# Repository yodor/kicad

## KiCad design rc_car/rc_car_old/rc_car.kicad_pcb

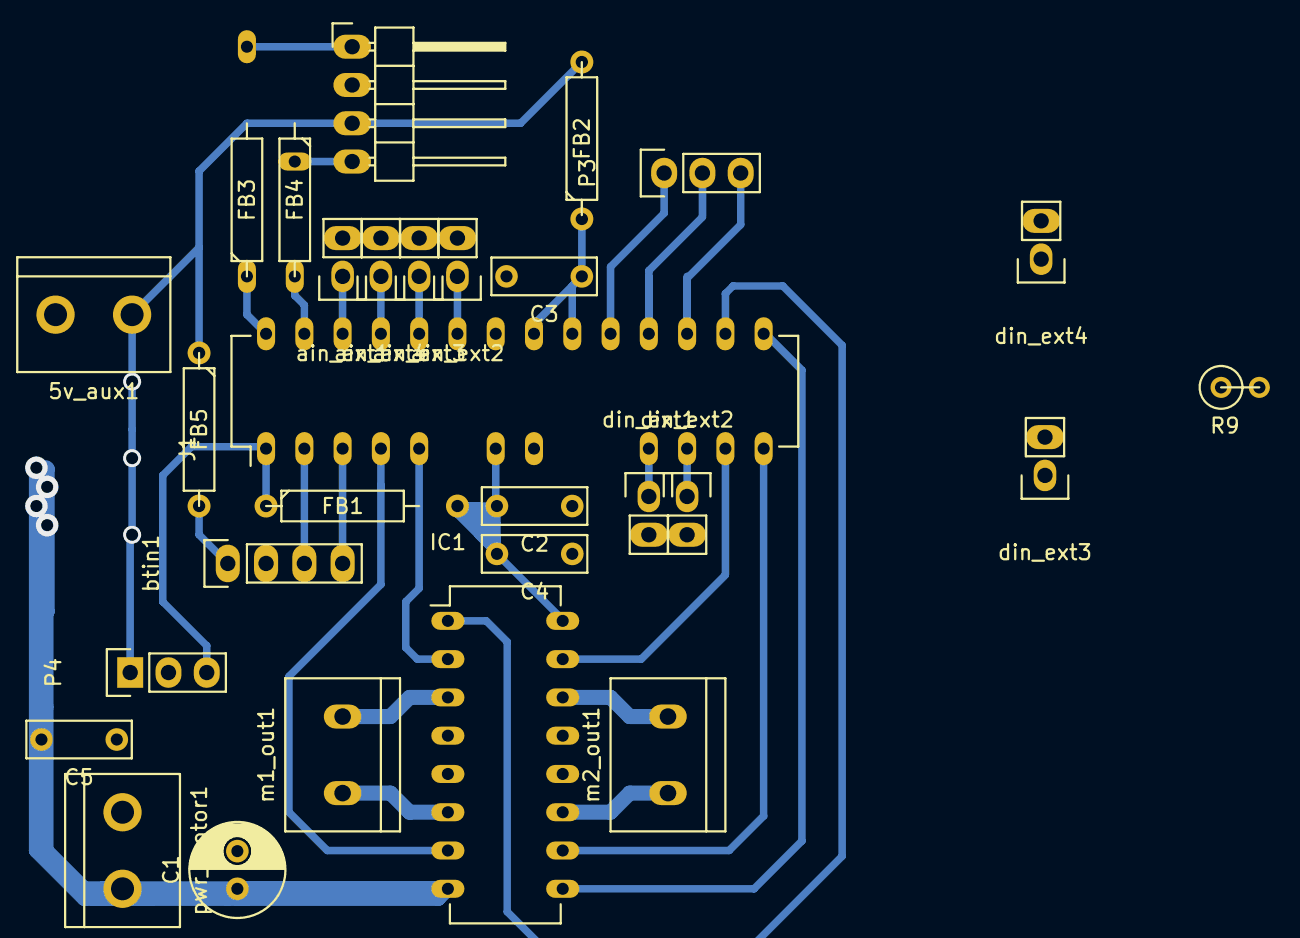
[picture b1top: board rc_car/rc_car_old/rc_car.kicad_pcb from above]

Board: 2 copper layers, 29 parts (0 on the bottom side), 33 nets.

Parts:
5v_aux1: CONN_2; bornier2
C1: 470uF; C_Radial_D6.3_L11.2_P2.5
C2, C3, C5: 100nF; C_Rect_L7_W2.5_P5
C4: 100n; C_Rect_L7_W2.5_P5
FB1, FB2, FB3, FB4, FB5: FILTER; R4
IC1: L293D; DIP-16_W7.62mm_LongPads
J1: Atmega328; DIP-28_W7.62mm_LongPads
P3, P4: CONN_01X03; Pin_Header_Straight_1x03
R9: 10K; R1
ain_ext1, ain_ext2, ain_ext3, ain_ext4: CONN_2; Pin_Header_Straight_1x02
btin1: CONN_4; Pin_Header_Straight_1x04
din_ext1, din_ext2, din_ext3, din_ext4: CONN_2; Pin_Header_Straight_1x02
i2c1: CONN_4; Pin_Header_Angled_1x04
m1_out1, m2_out1: CONN_2; bornier2
pwr_motor1: CONN_2; bornier2

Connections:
/5V: 5v_aux1.1, FB1.1, FB2.2, FB5.1, P4.1, R9.1, i2c1.3
/5V_FILTER: C2.2, C4.2, FB1.2, IC1.16, J1.7
/5V_FILTER_BT: FB5.2, btin1.1
/A0: J1.23, ain_ext2.1
/A1: J1.24, ain_ext3.1
/A2: J1.25, ain_ext4.1
/A3: J1.26, ain_ext1.1
/D1: J1.11, din_ext1.1
/D2: J1.12, din_ext2.1
/M1_EN: IC1.1, J1.16
/M1_L: IC1.2, J1.5
/M1_OUT_L: IC1.3, m1_out1.2
/M1_OUT_R: IC1.6, m1_out1.1
/M1_R: IC1.7, J1.4
/M2_EN: IC1.9, J1.15
/M2_L: IC1.15, J1.13
/M2_OUT_L: IC1.14, m2_out1.2
/M2_OUT_R: IC1.11, m2_out1.1
/M2_R: IC1.10, J1.14
/MISO: J1.18, P3.2
/MOSI: J1.17, P3.3
/RST: J1.1, P4.3, R9.2
/RX: J1.2, btin1.3
/SCK: J1.19, P3.1
/SCL: FB3.2, i2c1.1
/SDA: FB4.1, i2c1.4
/TX: J1.3, btin1.4
/VIN_MOTOR: C1.1, C5.2, IC1.8, pwr_motor1.2
GND: 5v_aux1.2, C2.1, C3.2, C4.1, C5.1, IC1.4, IC1.5, IC1.12, IC1.13, J1.8, J1.22, P4.2, ain_ext1.2, ain_ext2.2, ain_ext3.2, ain_ext4.2, btin1.2, din_ext1.2, din_ext2.2, din_ext3.2, din_ext4.2, i2c1.2
GNDREF: C1.2, pwr_motor1.1
unnamed: C3.1, FB2.1, J1.20, J1.21
unnamed: FB3.1, J1.28
unnamed: FB4.2, J1.27

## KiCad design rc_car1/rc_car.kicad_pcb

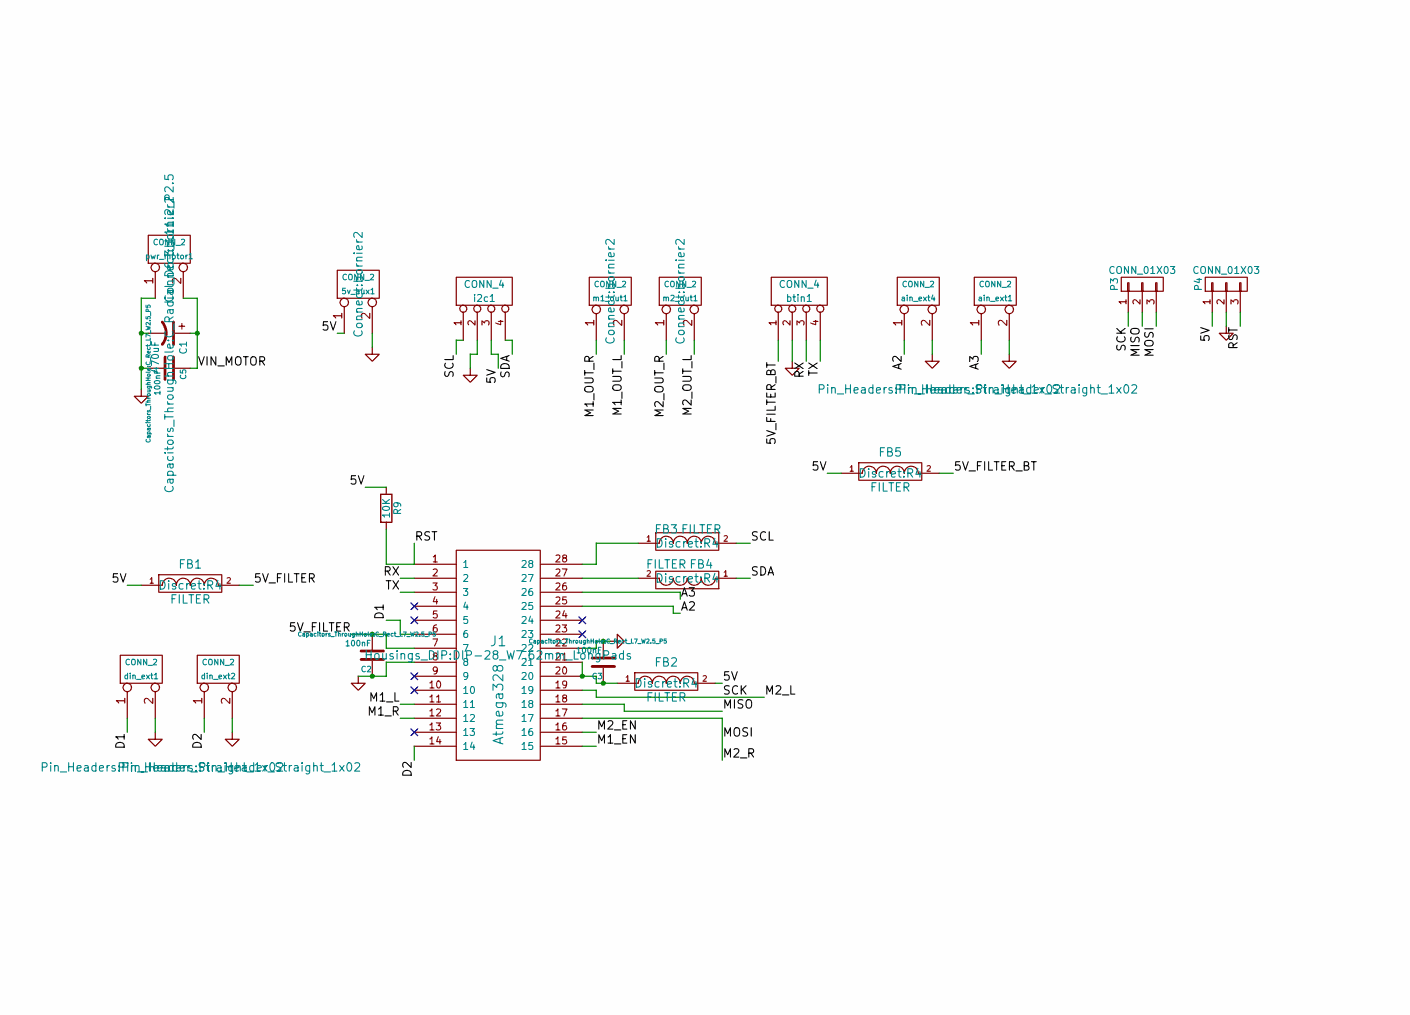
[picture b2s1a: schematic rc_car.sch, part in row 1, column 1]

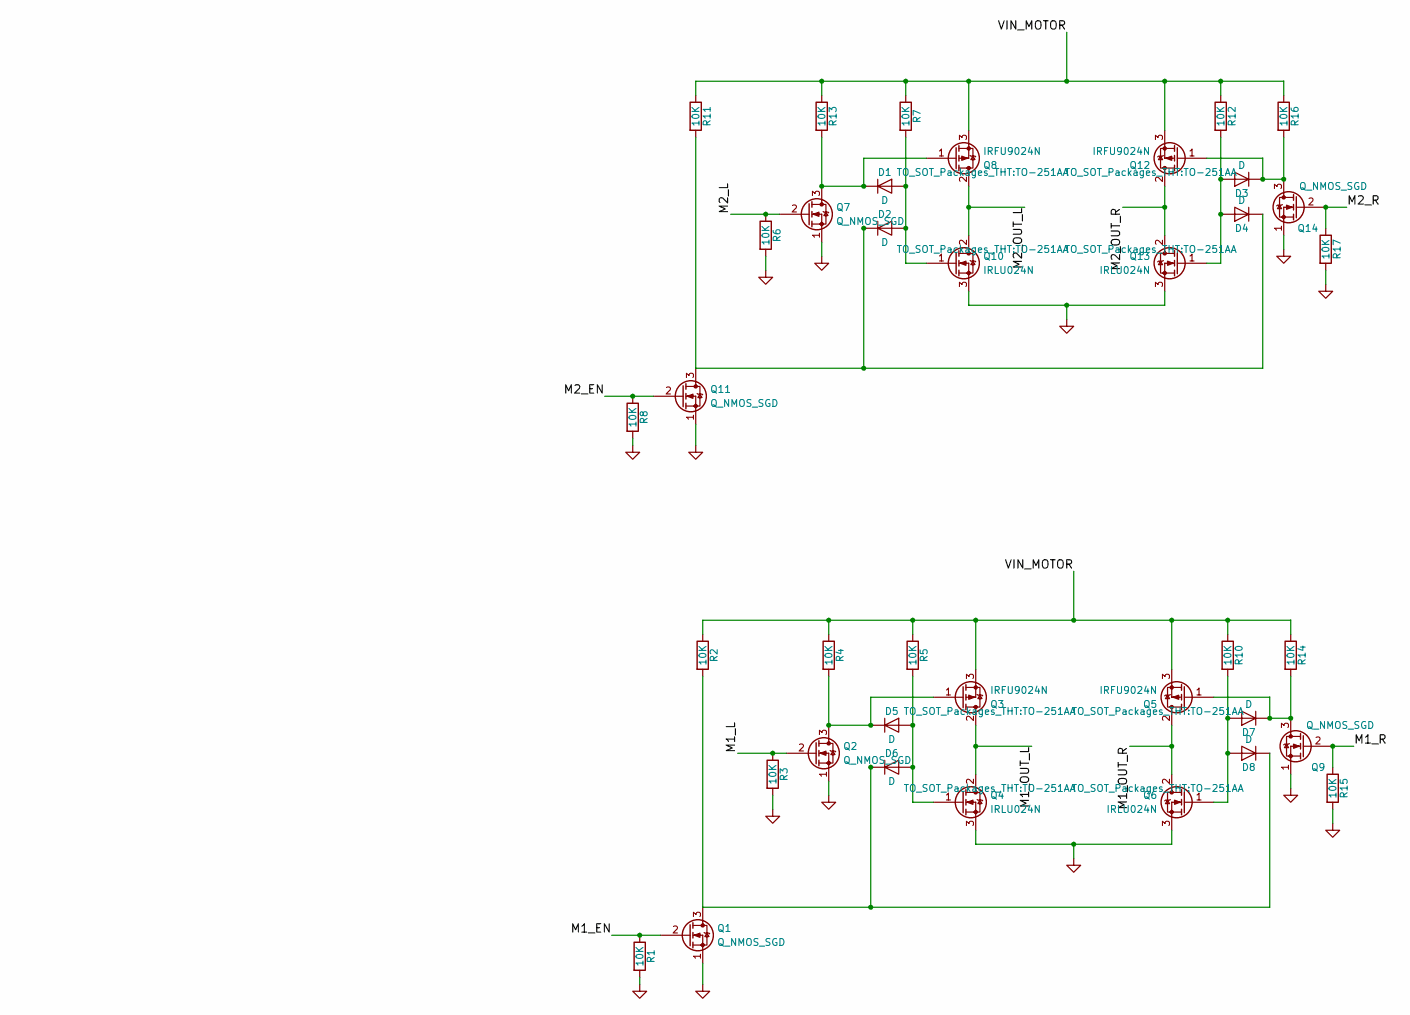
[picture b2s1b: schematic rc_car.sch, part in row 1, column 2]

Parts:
5v_aux1: CONN_2; bornier2
C1: 470uF; C_Radial_D6.3_L11.2_P2.5
C2, C3, C5: 100nF; C_Rect_L7_W2.5_P5
D1, D2, D3, D4, D5, D6, D7, D8: D; DO-41
FB1, FB2, FB3, FB4, FB5: FILTER; R4
J1: Atmega328; DIP-28_W7.62mm_LongPads
P3, P4: CONN_01X03; Pin_Header_Straight_1x03
Q1, Q2, Q7, Q9, Q11, Q14: Q_NMOS_SGD; TO-92_Inline_Narrow_Oval
Q3, Q5, Q8, Q12: IRFU9024N; TO-251AA
Q4, Q6, Q10, Q13: IRLU024N; TO-251AA
R1, R3, R6, R8, R14, R15, R16, R17: 10K; R1
R2, R4, R5, R7, R9, R10, R11, R12, R13: 10K; R4
ain_ext1, ain_ext4: CONN_2; Pin_Header_Straight_1x02
btin1: CONN_4; Pin_Header_Straight_1x04
din_ext1, din_ext2: CONN_2; Pin_Header_Straight_1x02
i2c1: CONN_4; Pin_Header_Angled_1x04
m1_out1, m2_out1: CONN_2; bornier2
pwr_motor1: CONN_2; bornier2

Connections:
/5V: 5v_aux1.1, FB1.1, FB2.2, FB5.1, P4.1, R9.1, i2c1.3
/5V_FILTER: C2.2, FB1.2, J1.7
/5V_FILTER_BT: FB5.2, btin1.1
/A2: J1.25, ain_ext4.1
/A3: J1.26, ain_ext1.1
/D1: J1.6, din_ext1.1
/D2: J1.14, din_ext2.1
/M1_EN: J1.15, Q1.2 (G), R1.1
/M1_L: J1.11, Q2.2 (G), R3.1
/M1_OUT_L: Q3.2 (D), Q4.2 (D), m1_out1.2 (PM)
/M1_OUT_R: Q5.2 (D), Q6.2 (D), m1_out1.1
/M1_R: J1.12, Q9.2 (G), R15.1
/M2_EN: J1.16, Q11.2 (G), R8.1
/M2_L: J1.19, P3.1, Q7.2 (G), R6.1
/M2_OUT_L: Q8.2 (D), Q10.2 (D), m2_out1.2 (PM)
/M2_OUT_R: Q12.2 (D), Q13.2 (D), m2_out1.1
/M2_R: J1.17, P3.3, Q14.2 (G), R17.1
/MISO: J1.18, P3.2
/RST: J1.1, P4.3, R9.2
/RX: J1.2, btin1.3
/SCL: FB3.2, i2c1.1
/SDA: FB4.1, i2c1.4
/TX: J1.3, btin1.4
/VIN_MOTOR: C1.1, C5.1, Q3.3 (S), Q5.3 (S), Q8.3 (S), Q12.3 (S), R2.1, R4.1, R5.1, R7.1, R10.1, R11.1, R12.1, R13.1, R14.1, R16.1, pwr_motor1.2 (PM)
GND: 5v_aux1.2 (PM), C1.2, C2.1, C3.2, C5.2, J1.8, J1.22, P4.2, Q1.1 (S), Q2.1 (S), Q4.3 (S), Q6.3 (S), Q7.1 (S), Q9.1 (S), Q10.3 (S), Q11.1 (S), Q13.3 (S), Q14.1 (S), R1.2, R3.2, R6.2, R8.2, R15.2, R17.2, ain_ext1.2 (PM), ain_ext4.2 (PM), btin1.2, din_ext1.2 (PM), din_ext2.2 (PM), i2c1.2, pwr_motor1.1
unnamed: C3.1, FB2.1, J1.20, J1.21
unnamed: D1.1 (K), Q7.3 (D), Q8.1 (G), R13.2
unnamed: D1.2 (A), D2.2 (A), Q10.1 (G), R7.2
unnamed: D2.1 (K), D4.1 (K), Q11.3 (D), R11.2
unnamed: D3.1 (K), Q12.1 (G), Q14.3 (D), R16.2
unnamed: D3.2 (A), D4.2 (A), Q13.1 (G), R12.2
unnamed: D5.1 (K), Q2.3 (D), Q3.1 (G), R4.2
unnamed: D5.2 (A), D6.2 (A), Q4.1 (G), R5.2
unnamed: D6.1 (K), D8.1 (K), Q1.3 (D), R2.2
unnamed: D7.1 (K), Q5.1 (G), Q9.3 (D), R14.2
unnamed: D7.2 (A), D8.2 (A), Q6.1 (G), R10.2
unnamed: FB3.1, J1.28
unnamed: FB4.2, J1.27

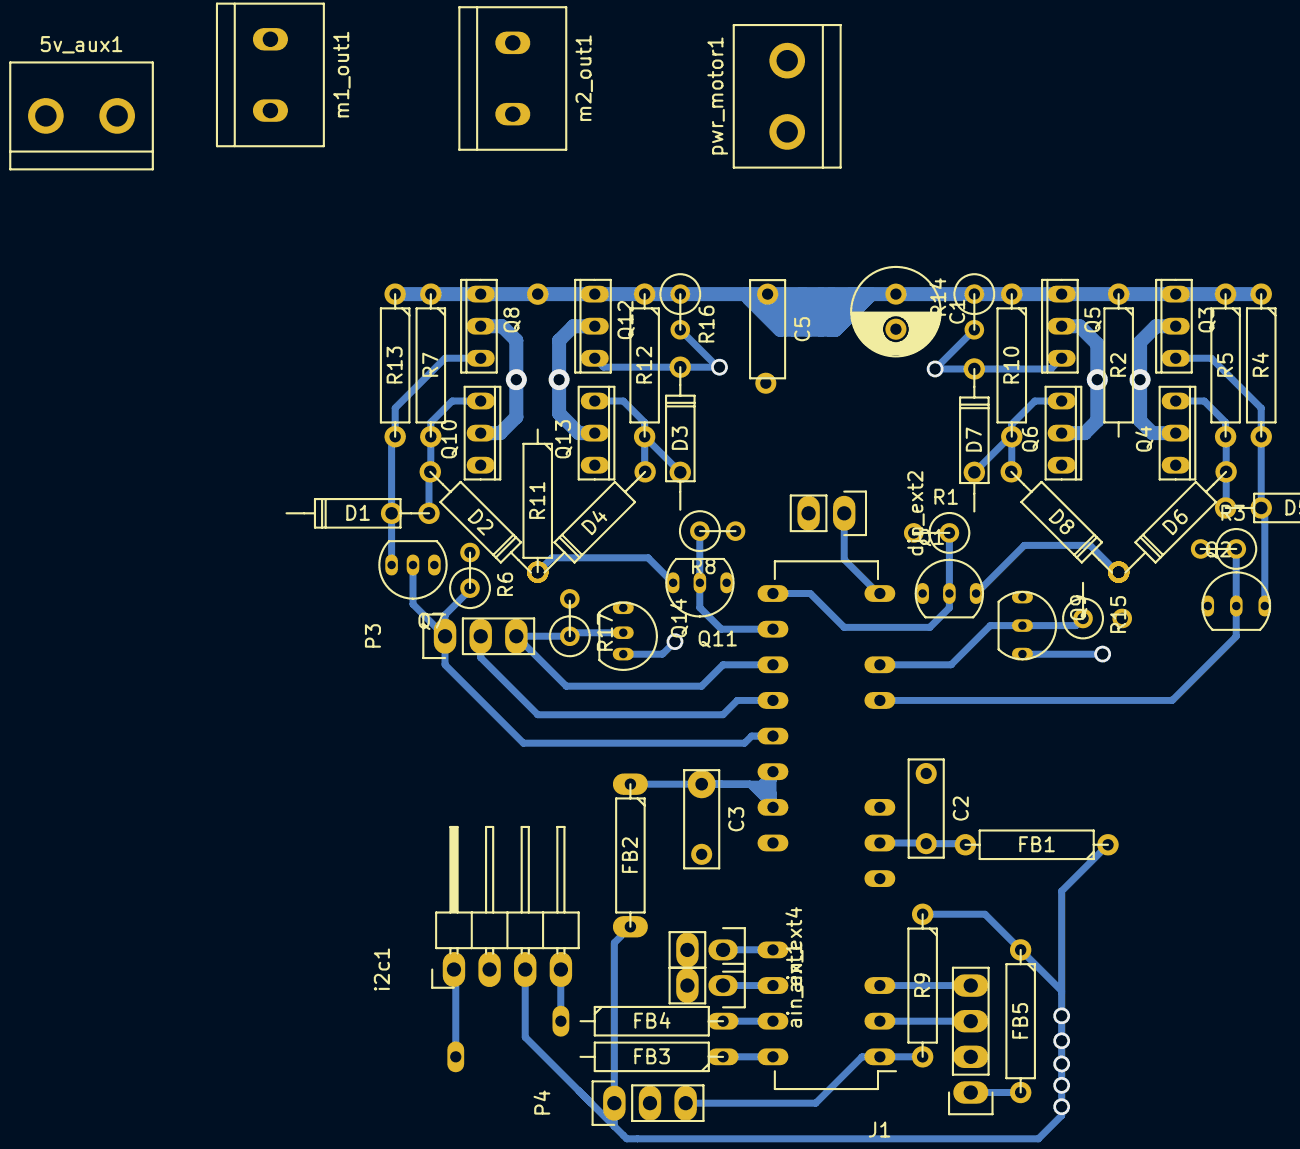
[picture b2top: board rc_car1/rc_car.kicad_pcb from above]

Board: 2 copper layers, 60 parts (0 on the bottom side), 37 nets.

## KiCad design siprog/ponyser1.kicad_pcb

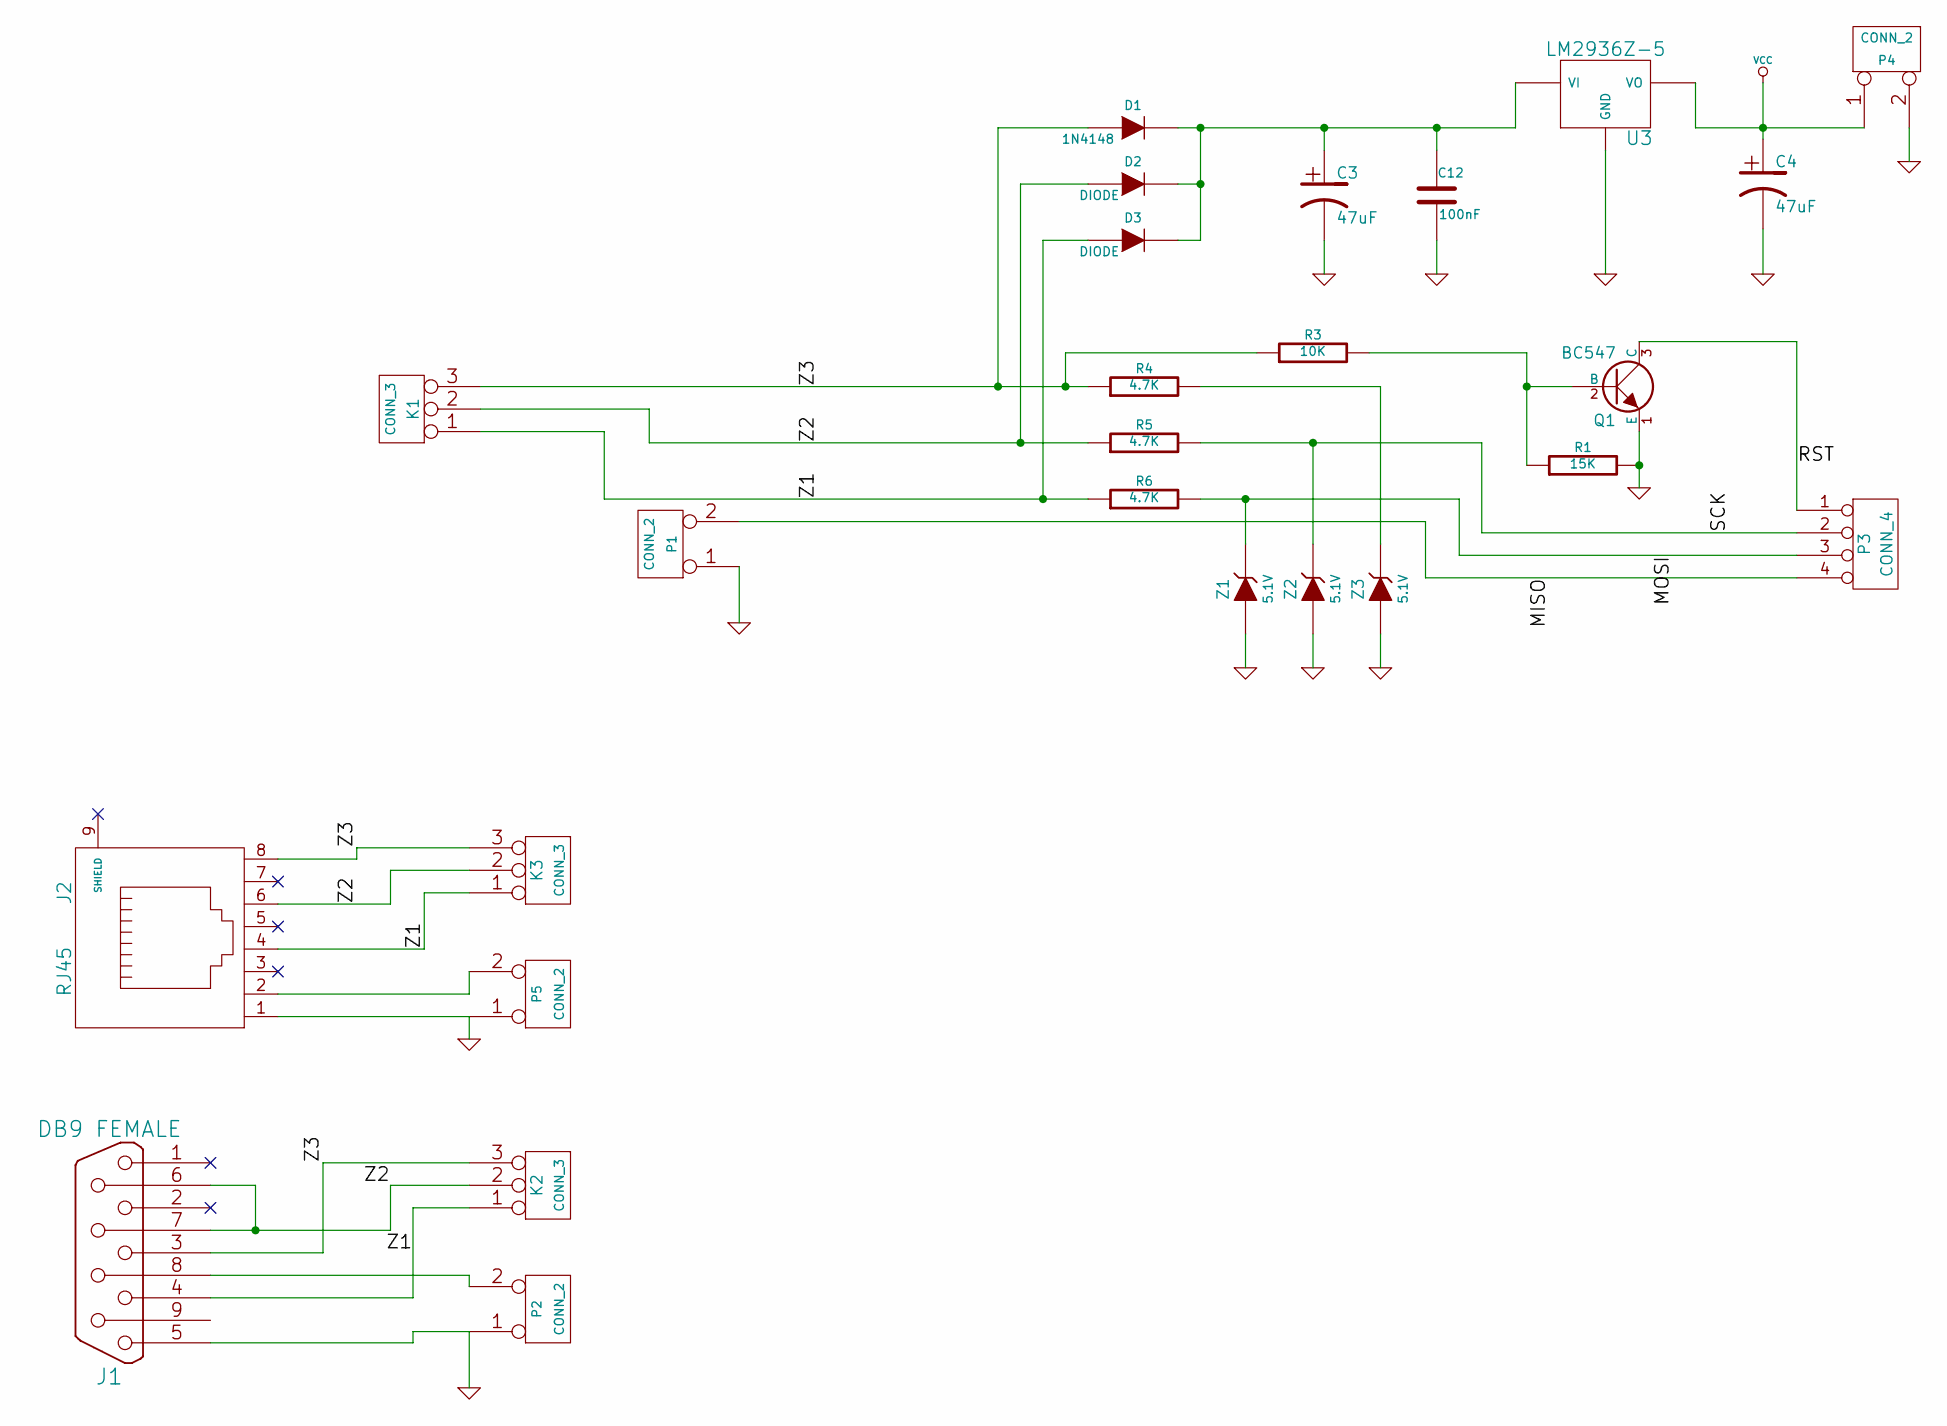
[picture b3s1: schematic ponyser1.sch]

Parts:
C3, C4: 47uF
C12: 100nF
D1: 1N4148
D2, D3: DIODE
J1: DB9 FEMALE
J2: RJ45
K1, K2, K3: CONN_3
P1, P2, P4, P5: CONN_2
P3: CONN_4
Q1: BC547
R1: 15K
R3: 10K
R4, R5, R6: 4.7K
U3: LM2936Z-5
Z1, Z2, Z3: 5.1V

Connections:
/MISO: P1.2 (PM), P3.4
/MOSI: P3.3, R6.2, Z1.2 (K)
/RST: P3.1, Q1.3 (C)
/SCK: P3.2, R5.2, Z2.2 (K)
/Z1: D3.1 (A), J1.4, J2.4, K1.1, K2.1, K3.1, R6.1
/Z2: D2.1 (A), J1.6, J1.7, J2.6, K1.2 (PM), K2.2 (PM), K3.2 (PM), R5.1
/Z3: D1.1 (A), J1.3, J2.8, K1.3, K2.3, K3.3, R3.1, R4.1
GND: C3.2, C4.2, C12.2, J1.5, J2.1, P1.1, P2.1, P4.2 (PM), P5.1, Q1.1 (E), R1.2, U3.GND, Z1.1 (A), Z2.1 (A), Z3.1 (A)
unnamed: Q1.2 (B), R1.1, R3.2
unnamed: C3.1, C12.1, D1.2 (K), D2.2 (K), D3.2 (K), U3.VI
unnamed: J2.2, P5.2 (PM)
unnamed: J1.8, P2.2 (PM)
unnamed: R4.2, Z3.2 (K)
VCC: C4.1, P4.1, U3.VO

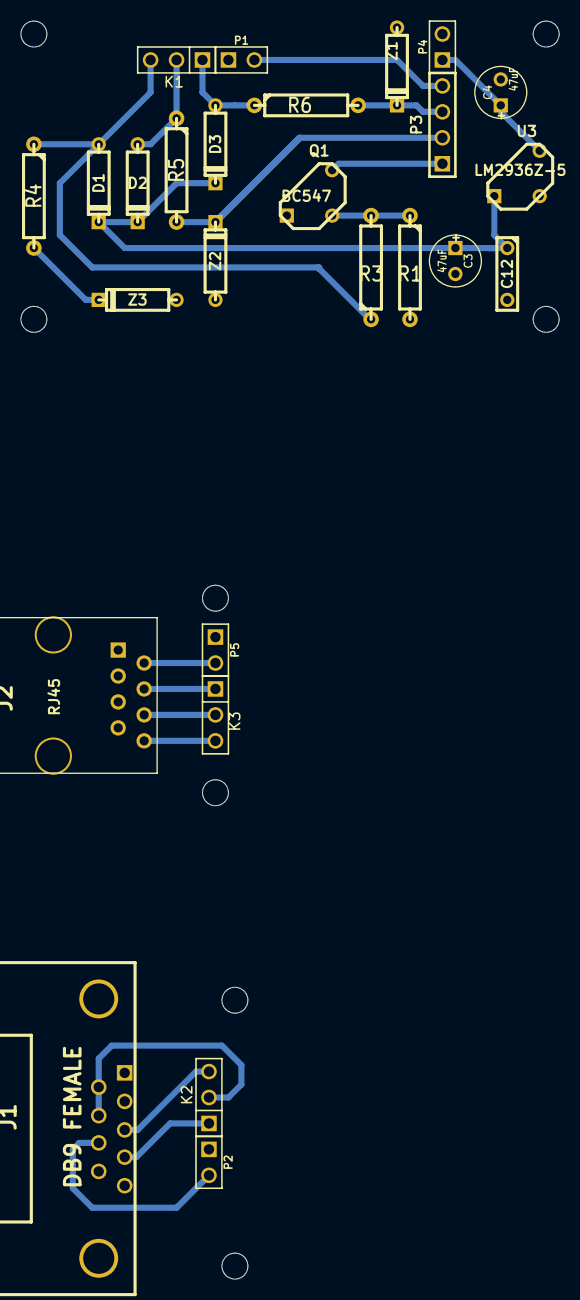
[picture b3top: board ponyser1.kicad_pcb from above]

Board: 2 copper layers, 52.7 x 123.2 mm, 26 parts (0 on the bottom side), 14 nets.

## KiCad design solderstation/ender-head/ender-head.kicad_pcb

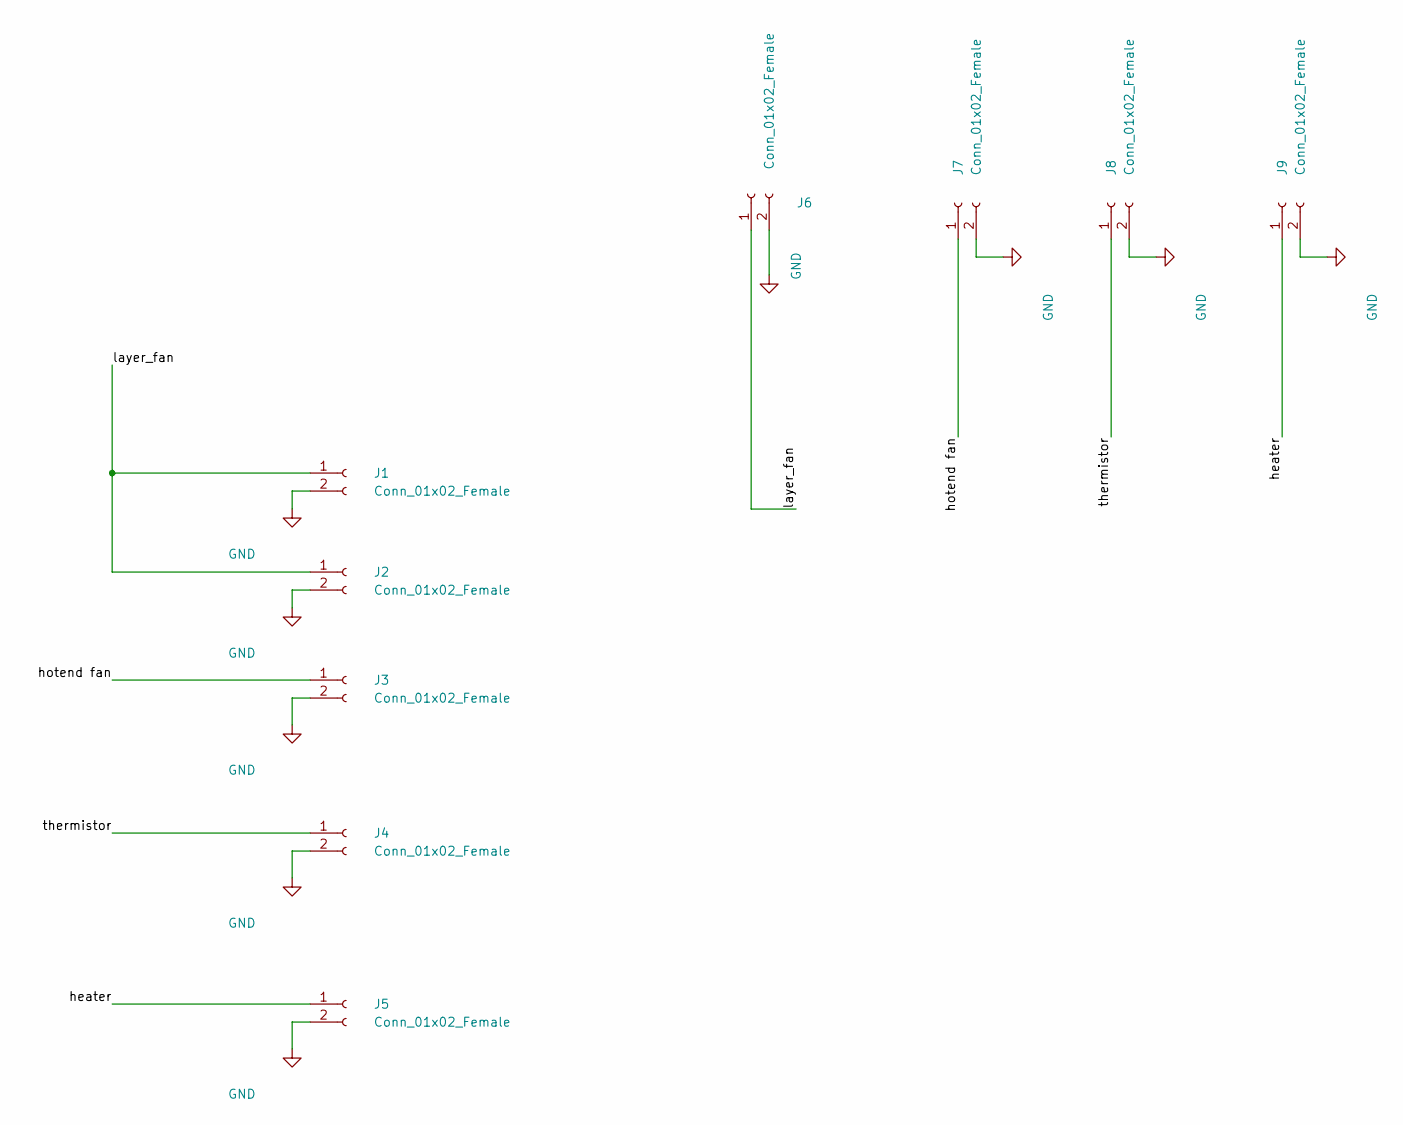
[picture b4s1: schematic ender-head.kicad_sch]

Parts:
J1, J2, J3, J4, J5: Conn_01x02_Female; TerminalBlock_bornier-2_P5.08mm
J6, J7, J8: Conn_01x02_Female; PinHeader_1x02_P2.54mm_Vertical
J9: Conn_01x02_Female; AMASS_XT60-M_1x02_P7.20mm_Vertical

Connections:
/heater: J5.1, J9.1
/hotend fan: J3.1, J7.1
/layer_fan: J1.1, J2.1, J6.1
/thermistor: J4.1, J8.1
GND: J1.2, J2.2, J3.2, J4.2, J5.2, J6.2, J7.2, J8.2, J9.2

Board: 2 copper layers, 9 parts (0 on the bottom side), 5 nets, no tracks yet.

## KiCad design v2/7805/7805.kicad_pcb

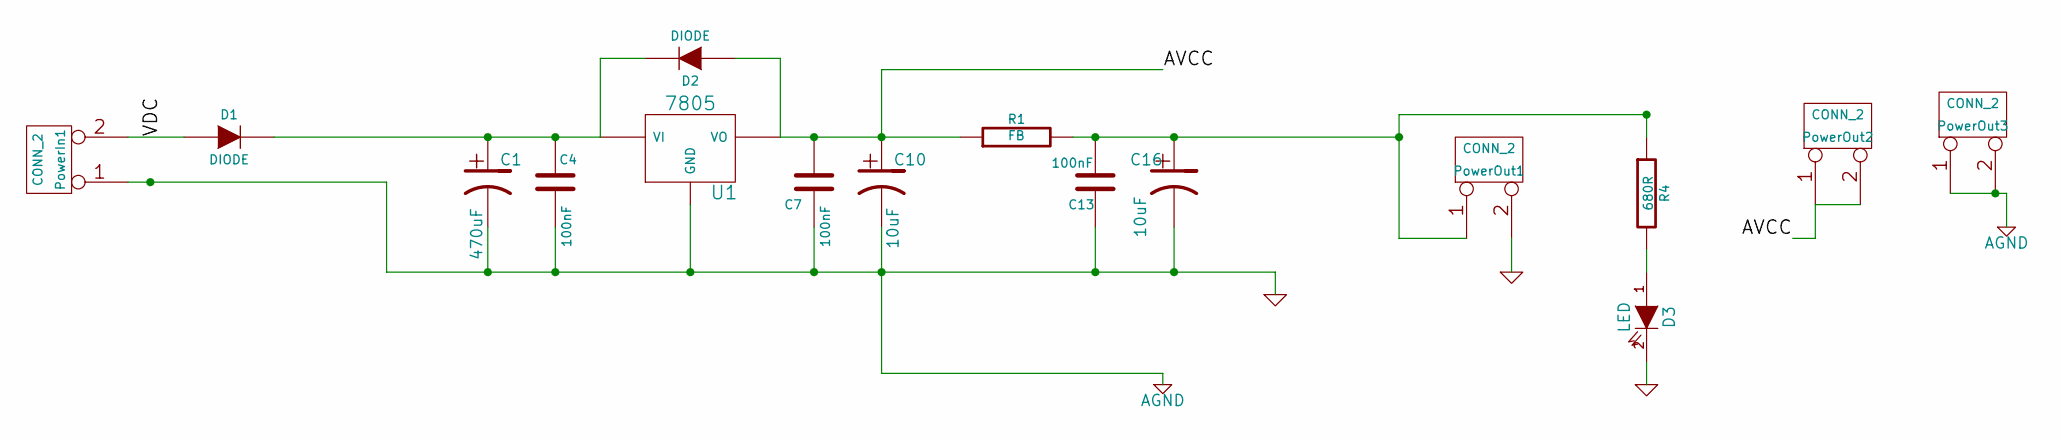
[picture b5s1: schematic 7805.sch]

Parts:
C1: 470uF
C4, C7, C13: 100nF
C10, C16: 10uF
D1, D2: DIODE
D3: LED
PowerIn1: CONN_2
PowerOut1, PowerOut2, PowerOut3: CONN_2
R1: FB
R4: 680R
U1: 7805

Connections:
/AVCC: C7.2, C10.1, D2.1 (A), PowerOut2.1, PowerOut2.2 (PM), R1.1, U1.VO
/VDC: D1.1 (A), PowerIn1.2 (PM)
AGND: C1.2, C4.1, C7.1, C10.2, C13.1, C16.2, D3.2 (K), PowerIn1.1, PowerOut1.2 (PM), PowerOut3.1, PowerOut3.2 (PM), U1.GND
unnamed: C13.2, C16.1, PowerOut1.1, R1.2, R4.1
unnamed: C1.1, C4.2, D1.2 (K), D2.2 (K), U1.VI
unnamed: D3.1 (A), R4.2

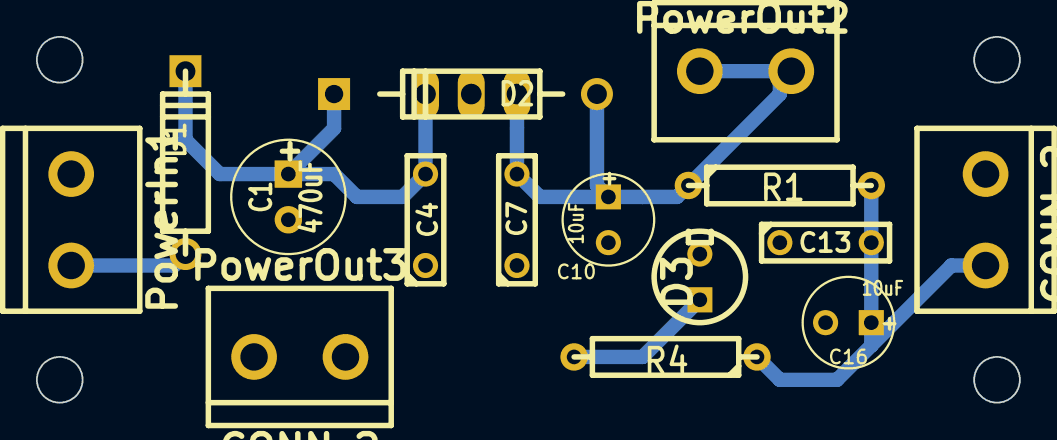
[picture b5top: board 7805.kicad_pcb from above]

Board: 2 copper layers, 54.6 x 20.3 mm, 16 parts (1 on the bottom side), 6 nets.

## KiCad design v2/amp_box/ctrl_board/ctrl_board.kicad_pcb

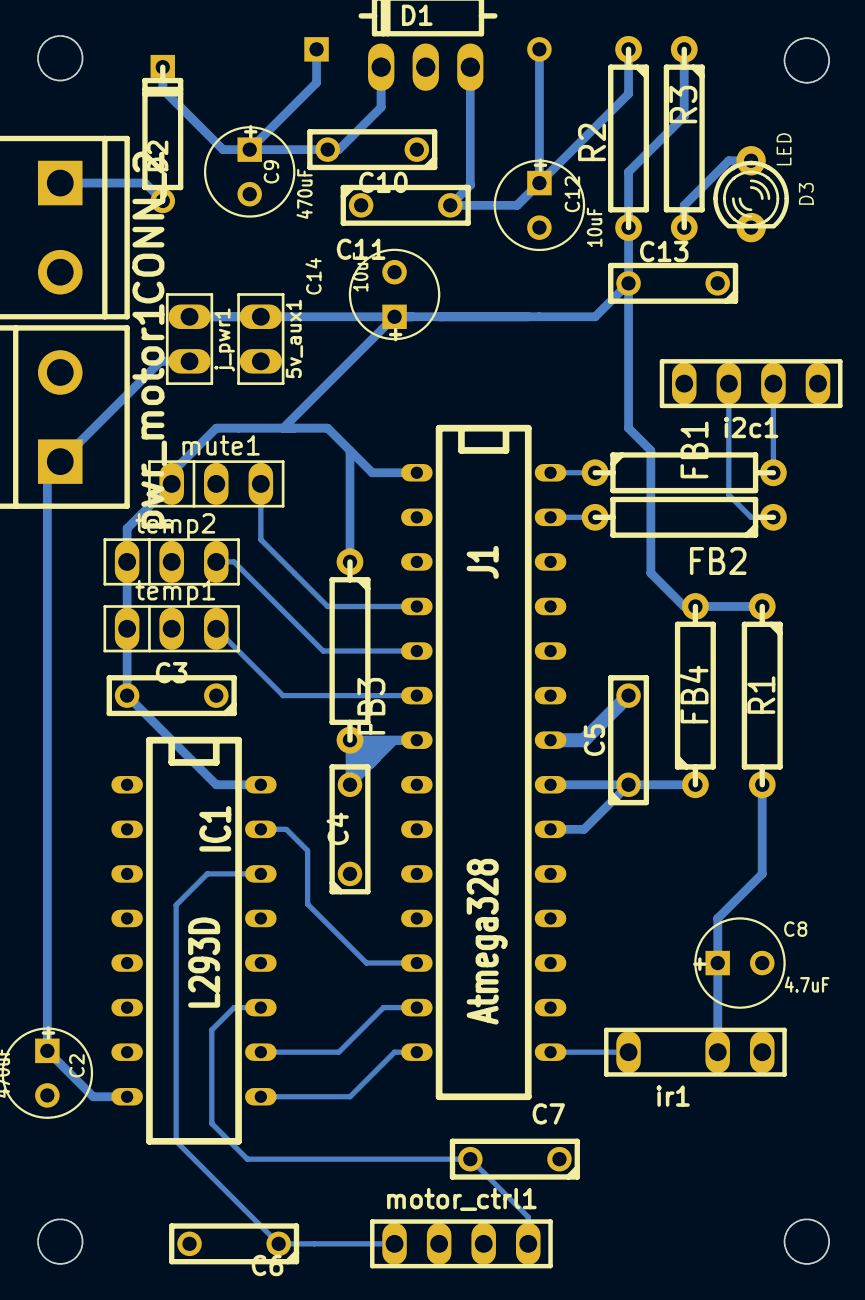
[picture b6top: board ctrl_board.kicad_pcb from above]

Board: 2 copper layers, 45.1 x 70.0 mm, 36 parts (0 on the bottom side), 23 nets.

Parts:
5v_aux1: CONN_2; PIN_ARRAY_2X1
12V1: CONN_2; bornier2
C2, C9: 470uF; C1V5
C3: 100n; C2
C4, C5, C10, C11, C13: 100nF; C2
C6, C7: 1uF; C2
C8: 4.7uF; C1V5
C12, C14: 10uF; C1V5
D1, D2: DIODE; D3
D3: LED; LED-3MM
FB1, FB2, FB3, FB4: FILTER; R4
IC1: L293D; DIP-16__300
J1: Atmega328; DIP-28__300
R1: 100R; R4
R2: FB; R4
R3: 680R; R4
U1: 7805; TO220_VERT
i2c1: CONN_4; PIN_ARRAY_4x1
ir1: CONN_4; PIN_ARRAY_4x1
j_pwr1: CONN_2; PIN_ARRAY_2X1
motor_ctrl1: CONN_4; PIN_ARRAY_4x1
mute1: CONN_3; PIN_ARRAY_3X1
pwr_motor1: CONN_2; bornier2
temp1, temp2: CONN_3; PIN_ARRAY_3X1

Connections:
/5V: 5v_aux1.1, C3.2, C13.2, C14.1, FB3.1, FB4.2, IC1.16, J1.1, R1.1, R2.2, R3.1, j_pwr1.1, mute1.1, temp1.1, temp2.1
/MOTOUT_L: C6.1, IC1.14, motor_ctrl1.1
/MOTOUT_R: C7.2, IC1.11, motor_ctrl1.4
/MOT_EN: IC1.9, J1.14
/MOT_L: IC1.15, J1.12
/MOT_R: IC1.10, J1.13
/MUTE_EN: J1.4, mute1.3
/SCL: FB1.2, i2c1.2
/SDA: FB2.1, i2c1.3
/TEMP_L: J1.5, temp2.3
/TEMP_R: J1.6, temp1.3
/VDC: 12V1.2, D2.1
/VIN_MOTOR: C2.1, IC1.8, j_pwr1.2, pwr_motor1.2
GND: 5v_aux1.2, 12V1.1, C2.2, C3.1, C4.1, C5.2, C6.2, C7.1, C8.2, C9.2, C10.1, C11.1, C12.2, C13.1, C14.2, D3.2, IC1.1, IC1.2, IC1.4, IC1.5, IC1.7, IC1.12, IC1.13, J1.8, J1.22, U1.GND, i2c1.1, i2c1.4, ir1.4, motor_ctrl1.2, motor_ctrl1.3, mute1.2, pwr_motor1.1, temp1.2, temp2.2
unnamed: FB1.1, J1.28
unnamed: FB2.2, J1.27
unnamed: J1.15, ir1.1
unnamed: D3.1, R3.2
unnamed: C8.1, R1.2, ir1.3
unnamed: C4.2, FB3.2, J1.7
unnamed: C5.1, FB4.1, J1.20, J1.21
unnamed: C9.1, C10.2, D1.2, D2.2, U1.VI
unnamed: C11.2, C12.1, D1.1, R2.1, U1.VO
